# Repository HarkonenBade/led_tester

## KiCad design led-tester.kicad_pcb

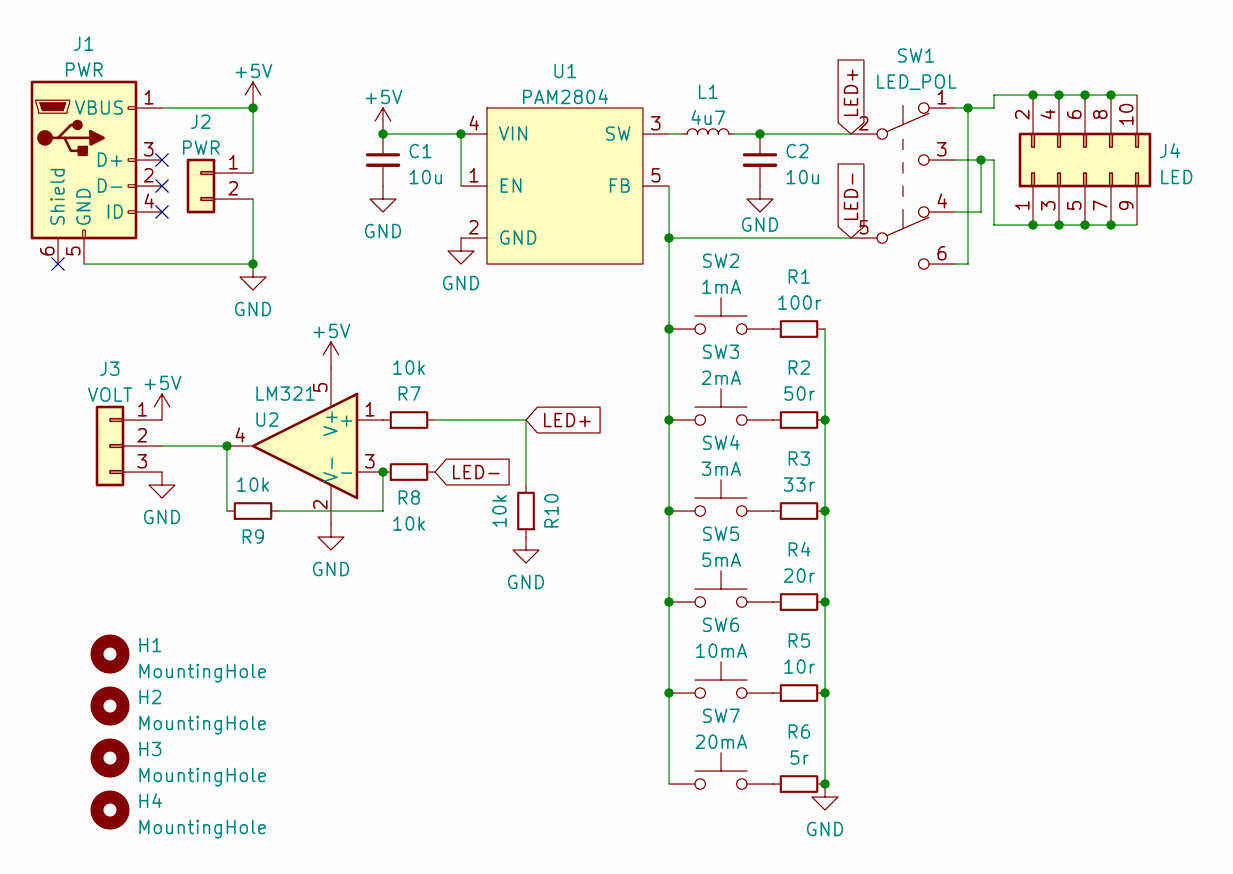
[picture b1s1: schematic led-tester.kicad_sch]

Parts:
C1, C2: 10u; C_0805_2012Metric; LCSC C1713
H1, H2, H3, H4: MountingHole; MountingHole_3.2mm_M3_DIN965
J1: PWR; USB_Micro-B_Molex-105017-0001
J2: PWR; JST_PH_S2B-PH-K_1x02_P2.00mm_Horizontal
J3: VOLT; JST_PH_S3B-PH-K_1x03_P2.00mm_Horizontal
J4: LED; PinSocket_2x05_P2.54mm_Vertical; LCSC 2xC718240
L1: 4u7; L_1008_2520Metric; LCSC C91237
R1: 100r; R_0603_1608Metric; LCSC C105588
R2: 50r; R_0603_1608Metric; LCSC C2759402
R3: 33r; R_0603_1608Metric; LCSC C108661
R4: 20r; R_0603_1608Metric; LCSC C22950
R5: 10r; R_0603_1608Metric; LCSC C109318
R6: 5r; R_0603_1608Metric; LCSC C25197
R7, R8, R9, R10: 10k; R_0603_1608Metric
SW1: LED_POL; OS202011MS2QS1
SW2: 1mA; SW_PUSH_6mm_H8mm; LCSC C2834903
SW3: 2mA; SW_PUSH_6mm_H8mm; LCSC C2834903
SW4: 3mA; SW_PUSH_6mm_H8mm; LCSC C2834903
SW5: 5mA; SW_PUSH_6mm_H8mm; LCSC C2834903
SW6: 10mA; SW_PUSH_6mm_H8mm; LCSC C2834903
SW7: 20mA; SW_PUSH_6mm_H8mm; LCSC C2834903
U1: PAM2804; TSOT-23-5; LCSC C71463
U2: LM321; SOT-23-5; LCSC C395460

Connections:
+5V: C1.1, J1.1 (VBUS), J2.1, J3.1, U1.1 (EN), U1.4 (VIN), U2.5 (V+)
GND: C1.2, C2.2, J1.5 (GND), J2.2, J3.3, R1.2, R2.2, R3.2, R4.2, R5.2, R6.2, R10.1, U1.2 (GND), U2.2 (V-)
LED+: C2.1, L1.2, R7.2, R10.2, SW1.2 (B)
LED-: R8.2, SW1.5 (B), SW2.1, SW3.1, SW4.1, SW5.1, SW6.1, SW7.1, U1.5 (FB)
unnamed: J3.2, R9.1, U2.4
unnamed: J4.1, J4.3, J4.5, J4.7, J4.9, SW1.3 (C), SW1.4 (A)
unnamed: J4.2, J4.4, J4.6, J4.8, J4.10, SW1.1 (A), SW1.6 (C)
unnamed: L1.1, U1.3 (SW)
unnamed: R1.1, SW2.2
unnamed: R2.1, SW3.2
unnamed: R3.1, SW4.2
unnamed: R4.1, SW5.2
unnamed: R5.1, SW6.2
unnamed: R6.1, SW7.2
unnamed: R7.1, U2.1 (+)
unnamed: R8.1, R9.2, U2.3 (-)

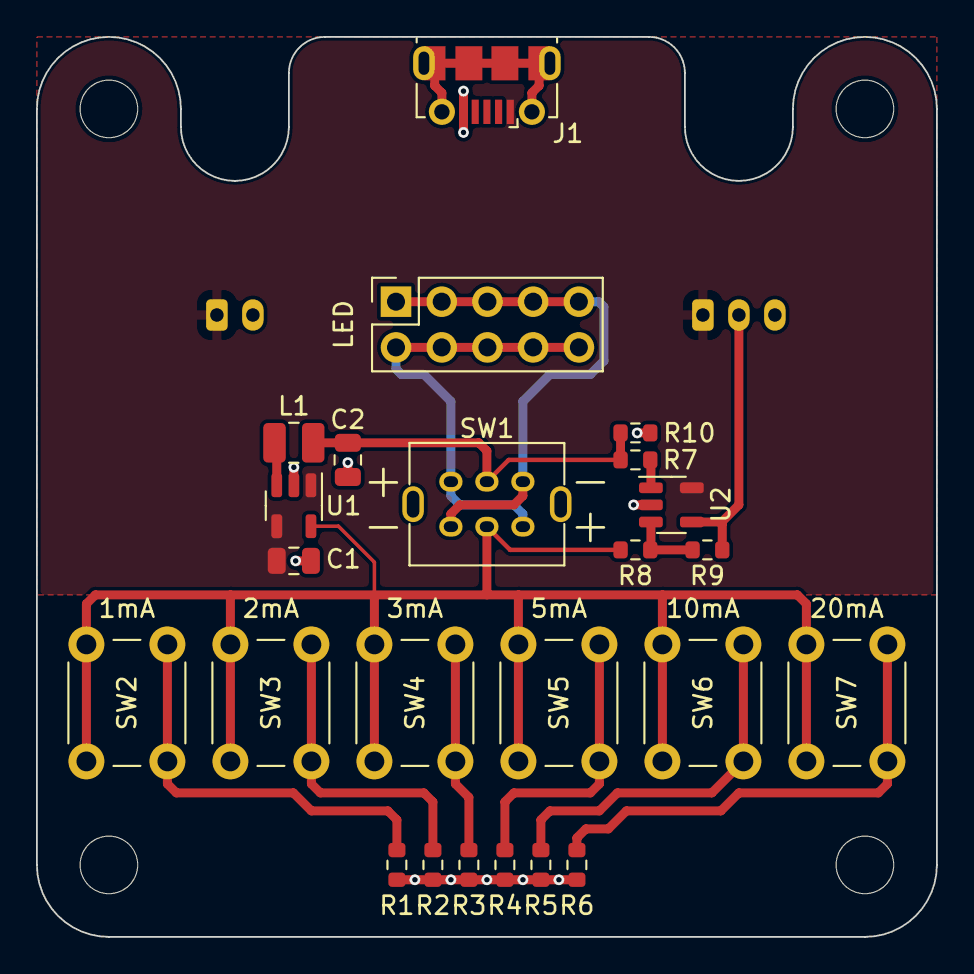
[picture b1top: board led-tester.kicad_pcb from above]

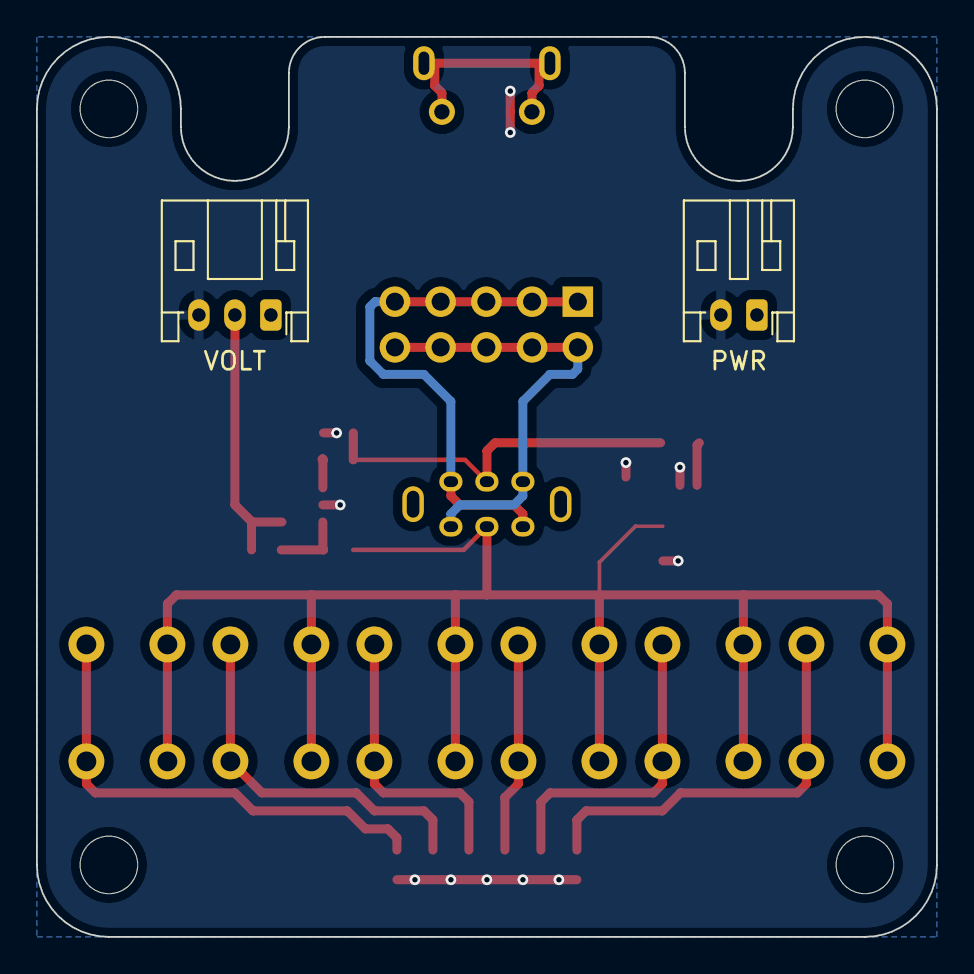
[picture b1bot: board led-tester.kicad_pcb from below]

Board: 2 copper layers, 50.0 x 50.0 mm, 30 parts (2 on the bottom side), 16 nets.

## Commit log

2022-05-06 Initial files
2022-05-15 Final tweaks and some part numbers
2022-05-15 gerbers
2022-05-16 Final tweaks and bom
2022-05-22 LCSC Part Numbers and BOM
